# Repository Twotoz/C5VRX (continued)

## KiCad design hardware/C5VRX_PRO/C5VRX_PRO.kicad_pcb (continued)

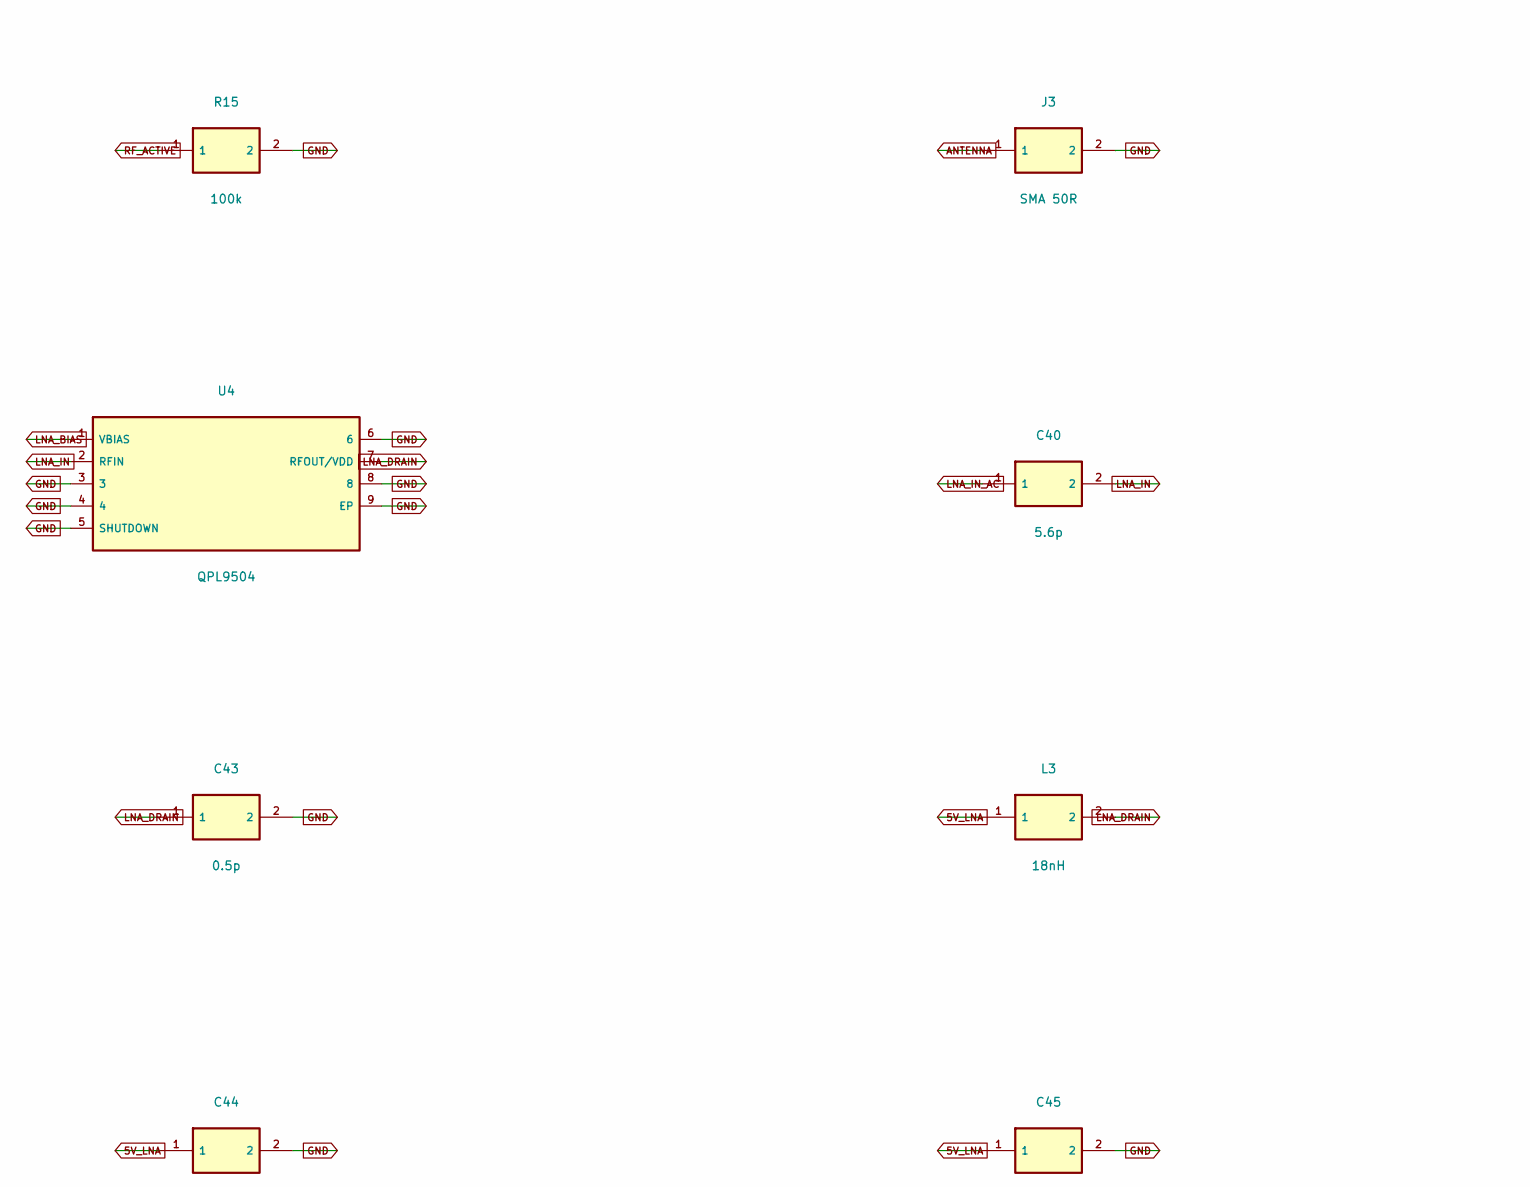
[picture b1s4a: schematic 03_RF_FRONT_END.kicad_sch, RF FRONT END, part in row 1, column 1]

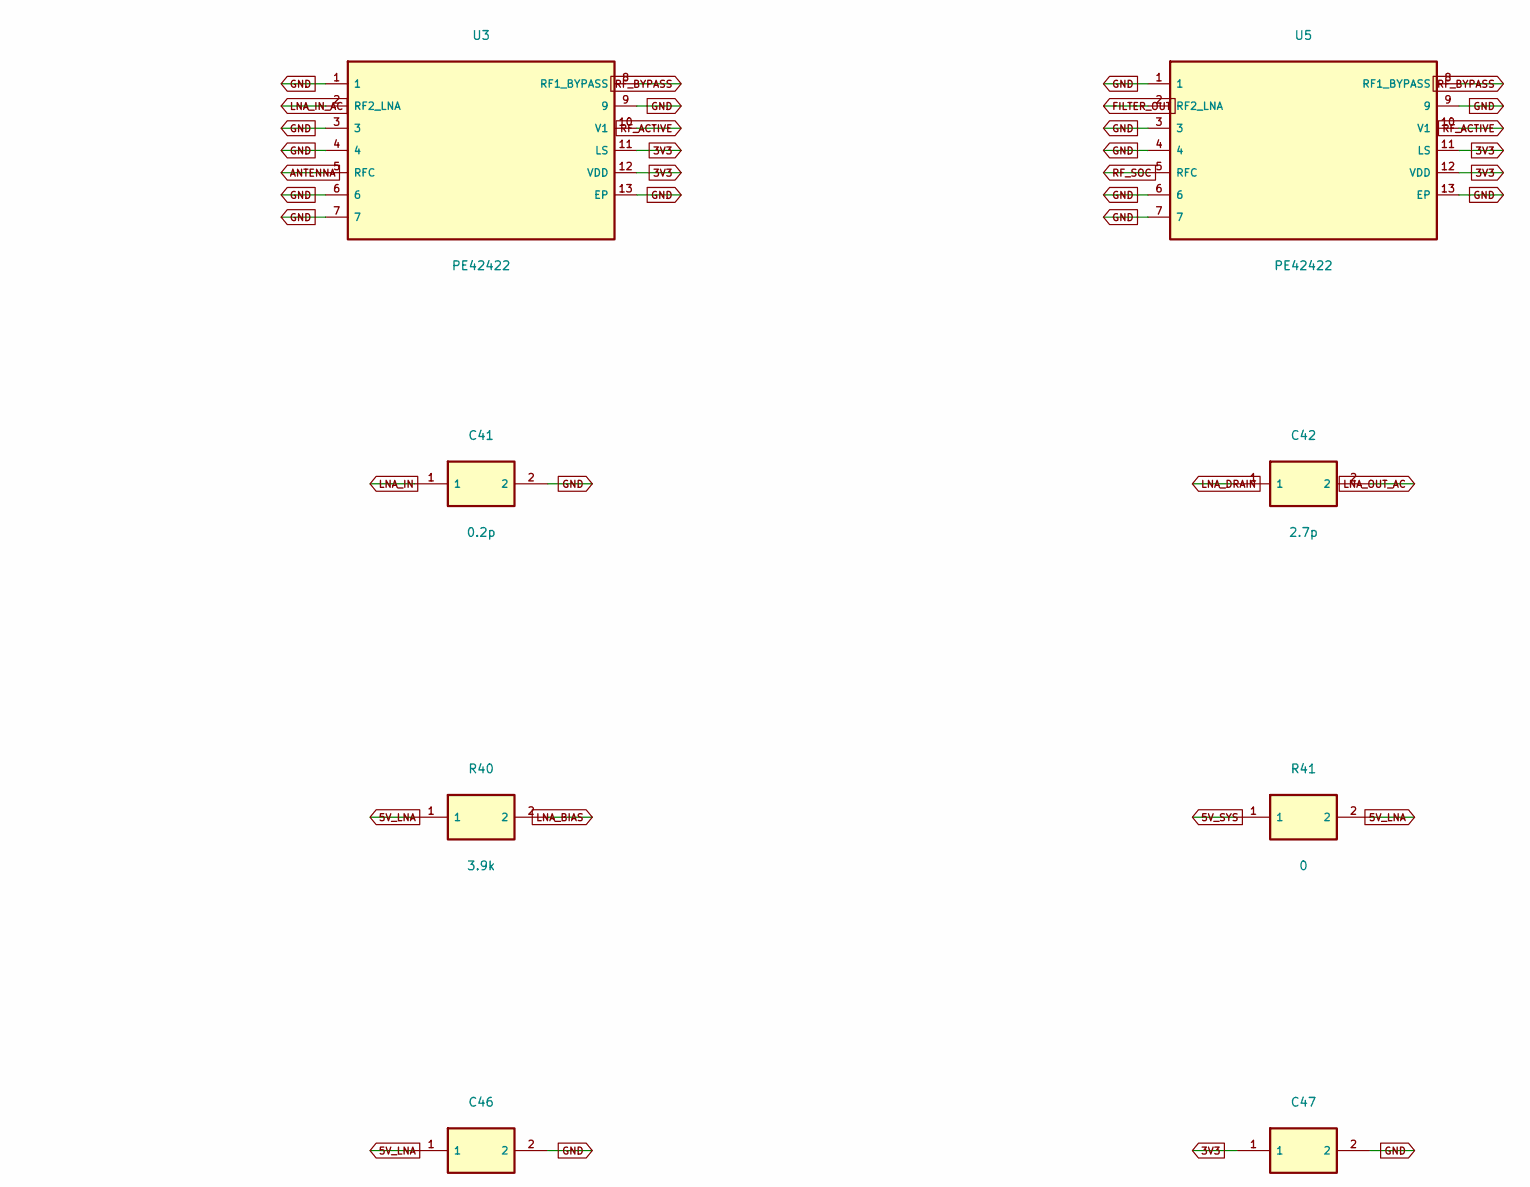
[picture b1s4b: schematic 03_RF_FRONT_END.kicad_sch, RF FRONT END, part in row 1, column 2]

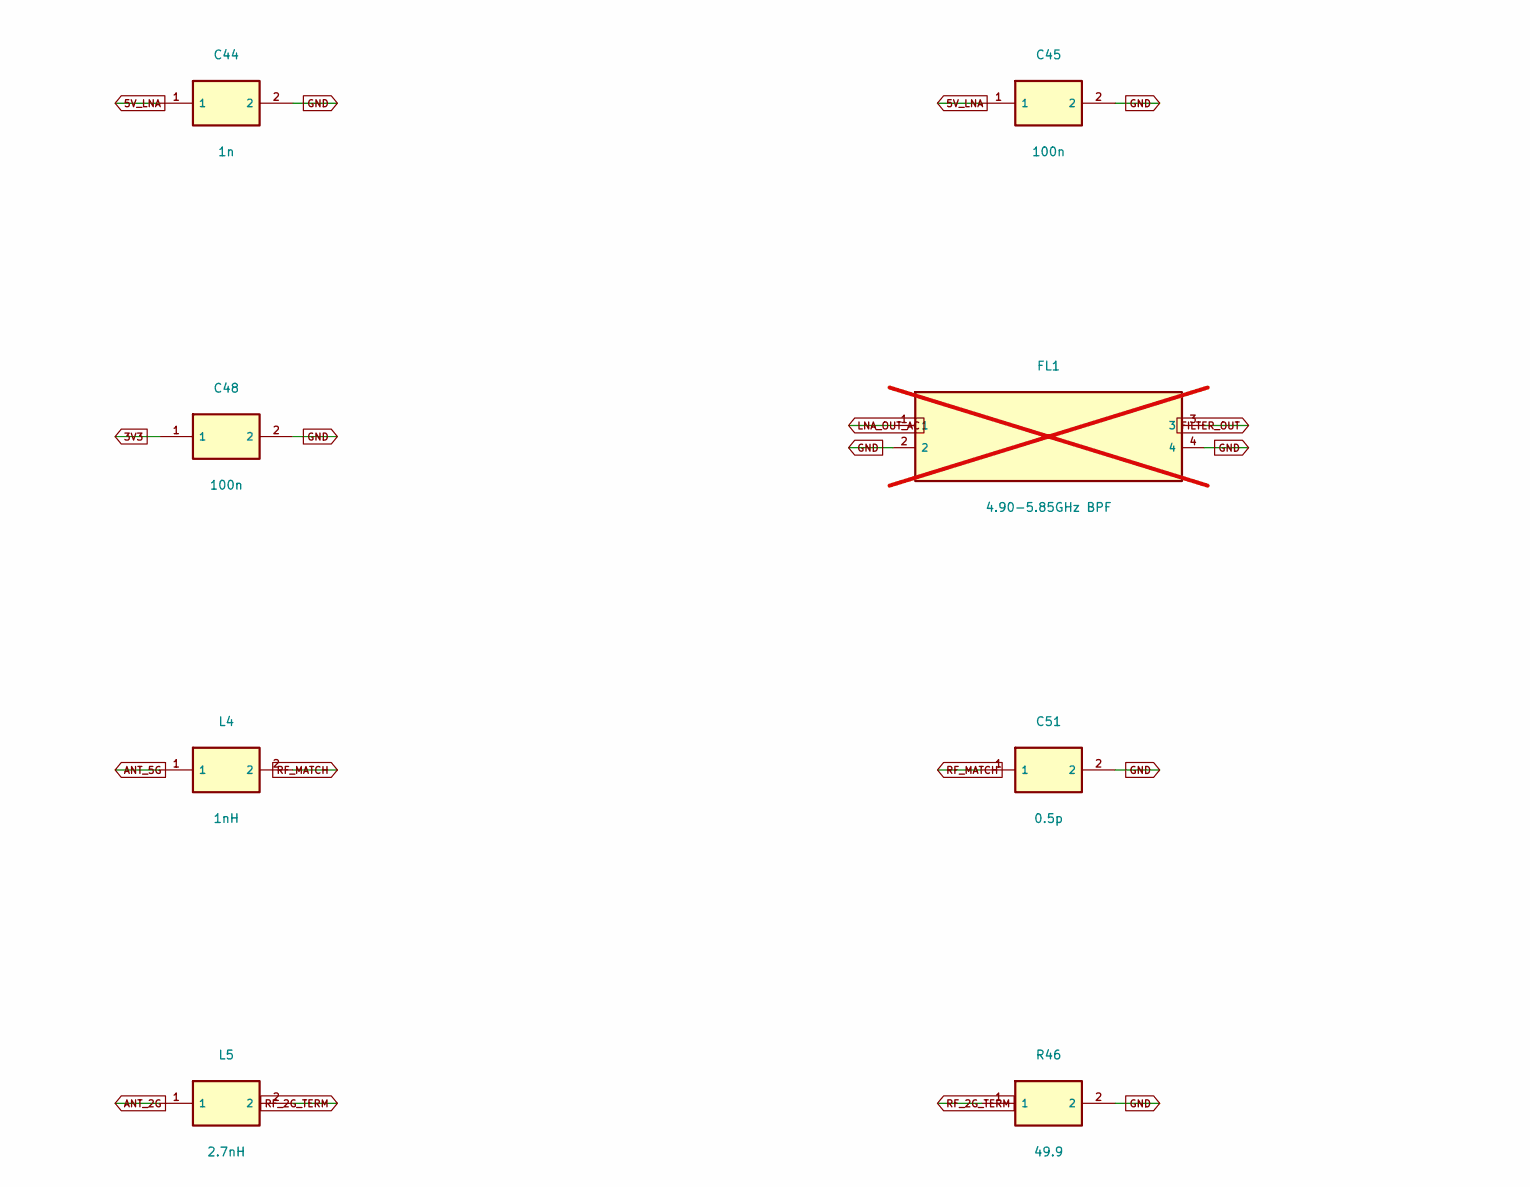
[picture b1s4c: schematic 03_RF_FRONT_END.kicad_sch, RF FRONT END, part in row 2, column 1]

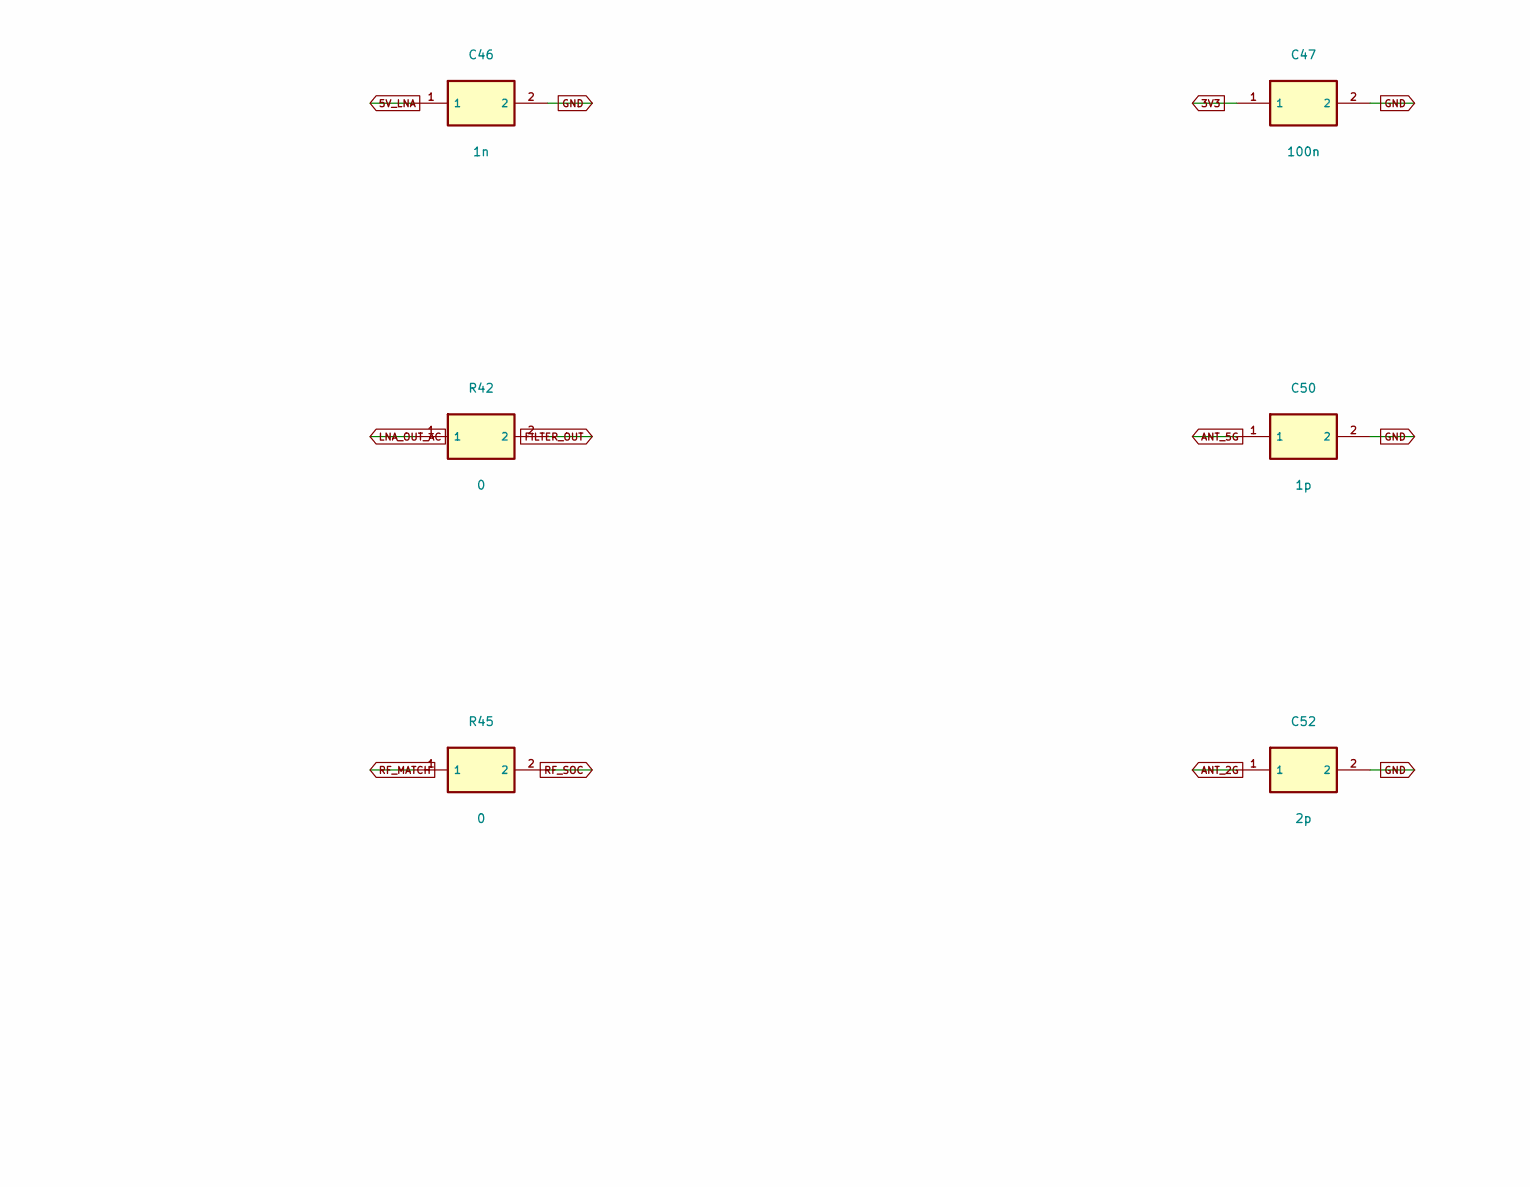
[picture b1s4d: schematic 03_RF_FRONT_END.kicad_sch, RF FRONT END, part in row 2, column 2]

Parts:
C40: 5.6p; Capacitor_SMD__C_0402_1005Metric; MPN GJM1555C1H5R6CB01D
C41: 0.2p; Capacitor_SMD__C_0402_1005Metric; MPN GJM1555C1HR20BB01D
C42: 2.7p; Capacitor_SMD__C_0402_1005Metric; MPN GJM1555C1H2R7CB01D
C43: 0.5p; Capacitor_SMD__C_0402_1005Metric; MPN GJM1555C1HR50BB01D
C44, C46: 1n; Capacitor_SMD__C_0402_1005Metric; MPN GRM155R71H102KA01D
C45, C47, C48: 100n; Capacitor_SMD__C_0402_1005Metric; MPN GRM155R71C104KA88D
C50: 1p; Capacitor_SMD__C_0201_0603Metric; MPN GRM0335C1H1R0CA01D
C51: 0.5p; Capacitor_SMD__C_0201_0603Metric; MPN GRM0335C1HR50BA01D
C52: 2p; Capacitor_SMD__C_0201_0603Metric; MPN GRM0335C1H2R0CA01D
FL1: 4.90-5.85GHz BPF; LFB215G37; MPN LFB215G37SG8A180; not fitted
J3: SMA 50R; Connector_Coaxial__SMA_Amphenol_132134_Vertical; MPN 132134
L3: 18nH; Inductor_SMD__L_0603_1608Metric; MPN 0603CS-18NXJRU
L4: 1nH; Inductor_SMD__L_0201_0603Metric; MPN LQP03TN1N0B02D
L5: 2.7nH; Inductor_SMD__L_0201_0603Metric; MPN LQP03TN2N7B02D
R15: 100k; Resistor_SMD__R_0402_1005Metric; MPN RC0402FR-07100KL
R40: 3.9k; Resistor_SMD__R_0402_1005Metric; MPN RC0402FR-073K9L
R41, R42, R45: 0; Resistor_SMD__R_0402_1005Metric; MPN RC0402JR-070RL
R46: 49.9; Resistor_SMD__R_0603_1608Metric; MPN RC0603FR-0749R9L
U3, U5: PE42422; PE42422_QFN12; MPN PE42422A-X
U4: QPL9504; QPL9504_DFN8; MPN QPL9504TR7

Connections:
3V3: C47.1, C48.1, U3.11 (LS), U3.12 (VDD), U5.11 (LS), U5.12 (VDD); also elsewhere on the board
5V_LNA: C44.1, C45.1, C46.1, L3.1, R40.1, R41.2
5V_SYS: R41.1; also elsewhere on the board
ANTENNA: J3.1, U3.5 (RFC)
ANT_2G: C52.1, L5.1; also elsewhere on the board
ANT_5G: C50.1, L4.1; also elsewhere on the board
FILTER_OUT: FL1.3, R42.2, U5.2 (RF2_LNA)
GND: C41.2, C43.2, C44.2, C45.2, C46.2, C47.2, C48.2, C50.2, C51.2, C52.2, FL1.2, FL1.4, J3.2, R15.2, R46.2, U3.1, U3.3, U3.4, U3.6, U3.7, U3.9, U3.13 (EP), U4.3, U4.4, U4.5 (SHUTDOWN), U4.6, U4.8, U4.9 (EP), U5.1, U5.3, U5.4, U5.6, U5.7, U5.9, U5.13 (EP); also elsewhere on the board
LNA_BIAS: R40.2, U4.1 (VBIAS)
LNA_DRAIN: C42.1, C43.1, L3.2, U4.7 (RFOUT/VDD)
LNA_IN: C40.2, C41.1, U4.2 (RFIN)
LNA_IN_AC: C40.1, U3.2 (RF2_LNA)
LNA_OUT_AC: C42.2, FL1.1, R42.1
RF_2G_TERM: L5.2, R46.1
RF_ACTIVE: R15.1, U3.10 (V1), U5.10 (V1); also elsewhere on the board
RF_BYPASS: U3.8 (RF1_BYPASS), U5.8 (RF1_BYPASS)
RF_MATCH: C51.1, L4.2, R45.1
RF_SOC: R45.2, U5.5 (RFC)

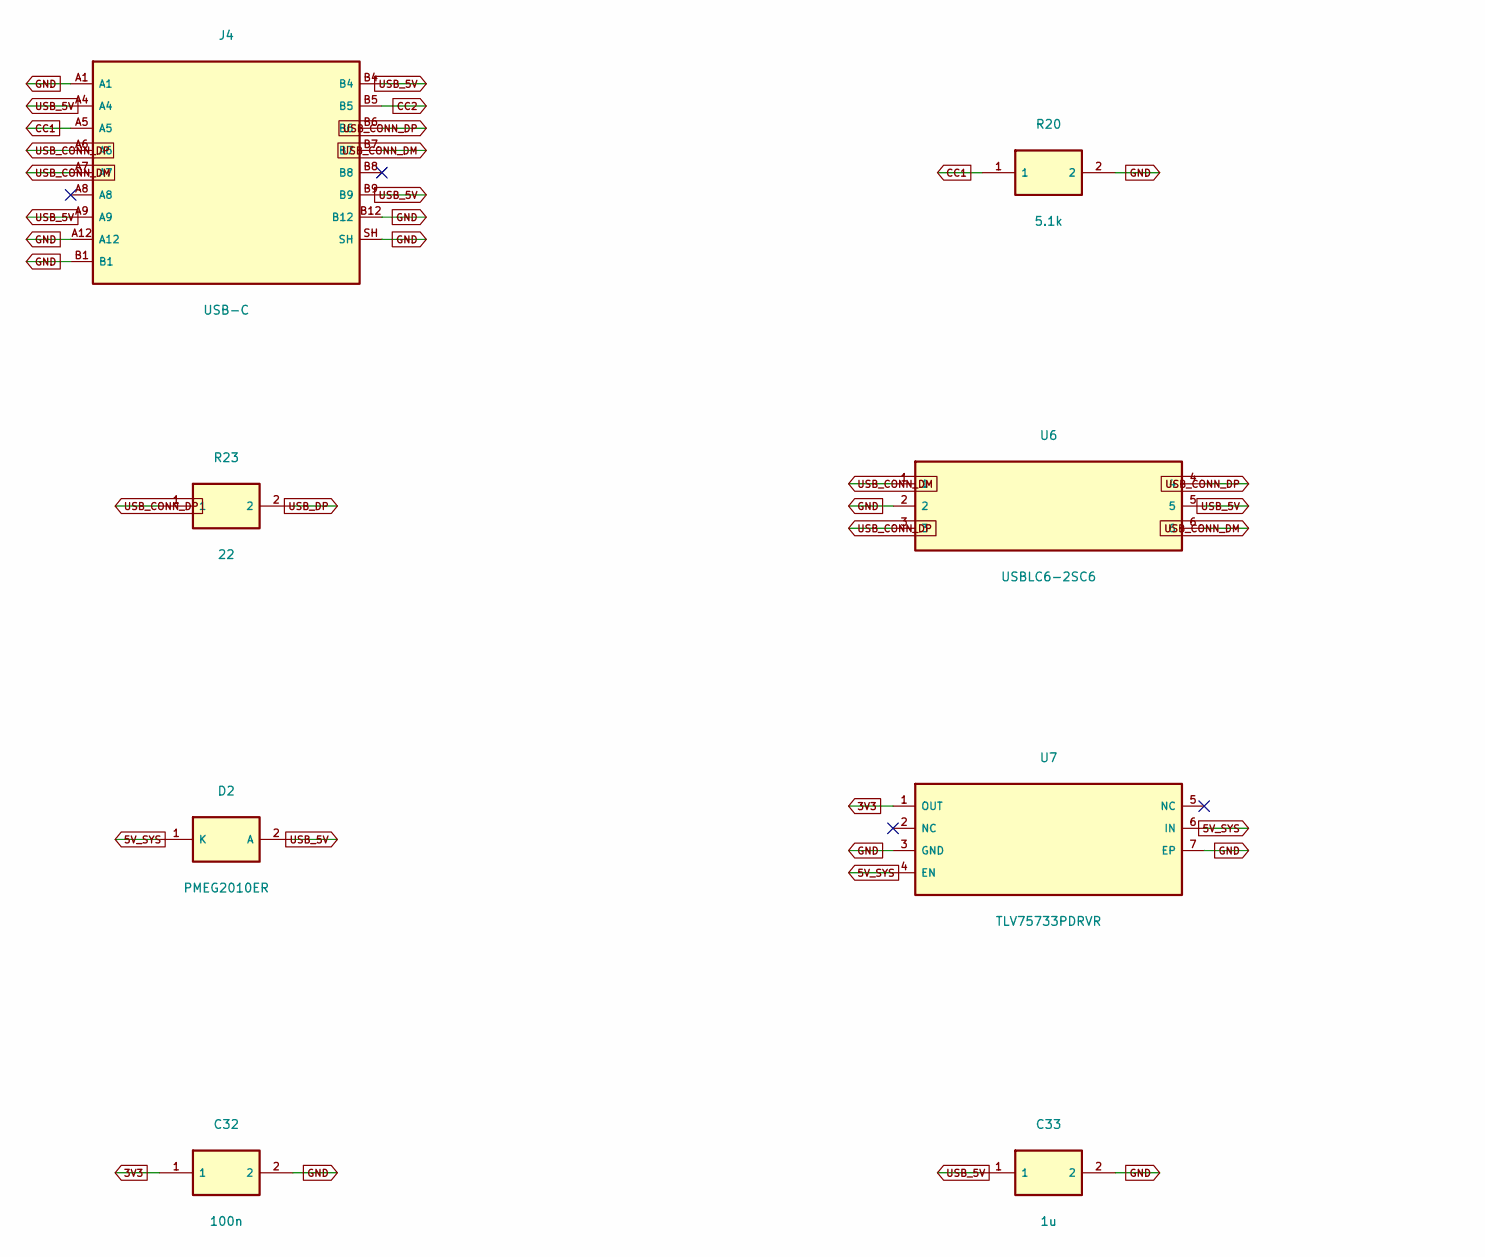
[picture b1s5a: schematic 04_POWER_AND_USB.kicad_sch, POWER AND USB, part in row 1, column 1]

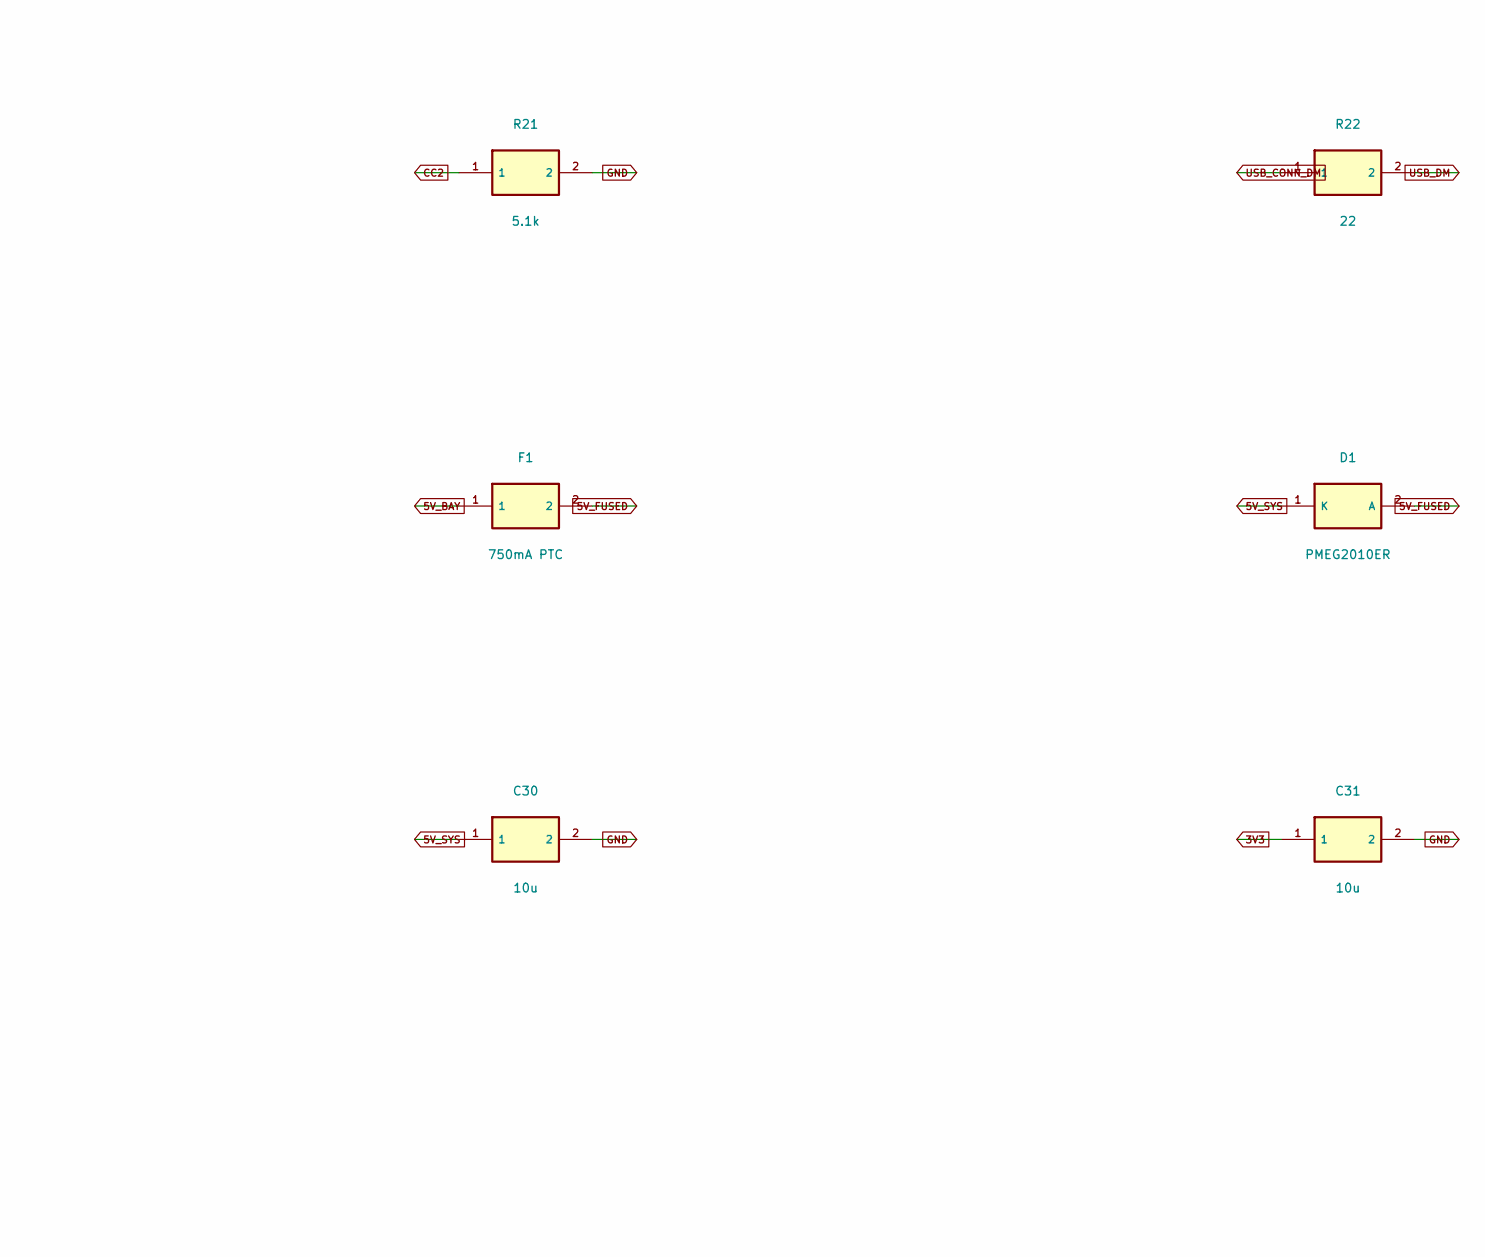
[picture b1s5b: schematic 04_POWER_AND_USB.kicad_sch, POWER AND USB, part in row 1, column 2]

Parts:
C30, C31: 10u; Capacitor_SMD__C_0603_1608Metric; MPN GRM188R61A106KE69D
C32: 100n; Capacitor_SMD__C_0402_1005Metric; MPN GRM155R71C104KA88D
C33: 1u; Capacitor_SMD__C_0402_1005Metric; MPN GRM155R61A105KE15D
D1, D2: PMEG2010ER; Diode_SMD__Nexperia_CFP3_SOD-123W; MPN PMEG2010ER,115
F1: 750mA PTC; Fuse__Fuse_1206_3216Metric; MPN 1206L075/13.2WR
J4: USB-C; Connector_USB__USB_C_Receptacle_HRO_TYPE-C-31-M-12; MPN TYPE-C-31-M-12
R20, R21: 5.1k; Resistor_SMD__R_0402_1005Metric; MPN RC0402FR-075K1L
R22, R23: 22; Resistor_SMD__R_0402_1005Metric; MPN RC0402FR-0722RL
U6: USBLC6-2SC6; Package_TO_SOT_SMD__SOT-23-6; MPN USBLC6-2SC6
U7: TLV75733PDRVR; Package_DFN_QFN__DFN-6-1EP_2x2mm_P0.65mm_EP1x1.6mm; MPN TLV75733PDRVR

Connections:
3V3: C31.1, C32.1, U7.1 (OUT); also elsewhere on the board
5V_BAY: F1.1; also elsewhere on the board
5V_FUSED: D1.2 (A), F1.2
5V_SYS: C30.1, D1.1 (K), D2.1 (K), U7.4 (EN), U7.6 (IN); also elsewhere on the board
CC1: J4.A5, R20.1
CC2: J4.B5, R21.1
GND: C30.2, C31.2, C32.2, C33.2, J4.A1, J4.A12, J4.B1, J4.B12, J4.SH, R20.2, R21.2, U6.2, U7.3 (GND), U7.7 (EP); also elsewhere on the board
USB_5V: C33.1, D2.2 (A), J4.A4, J4.A9, J4.B4, J4.B9, U6.5
USB_CONN_DM: J4.A7, J4.B7, R22.1, U6.1, U6.6
USB_CONN_DP: J4.A6, J4.B6, R23.1, U6.3, U6.4
USB_DM: R22.2; also elsewhere on the board
USB_DP: R23.2; also elsewhere on the board

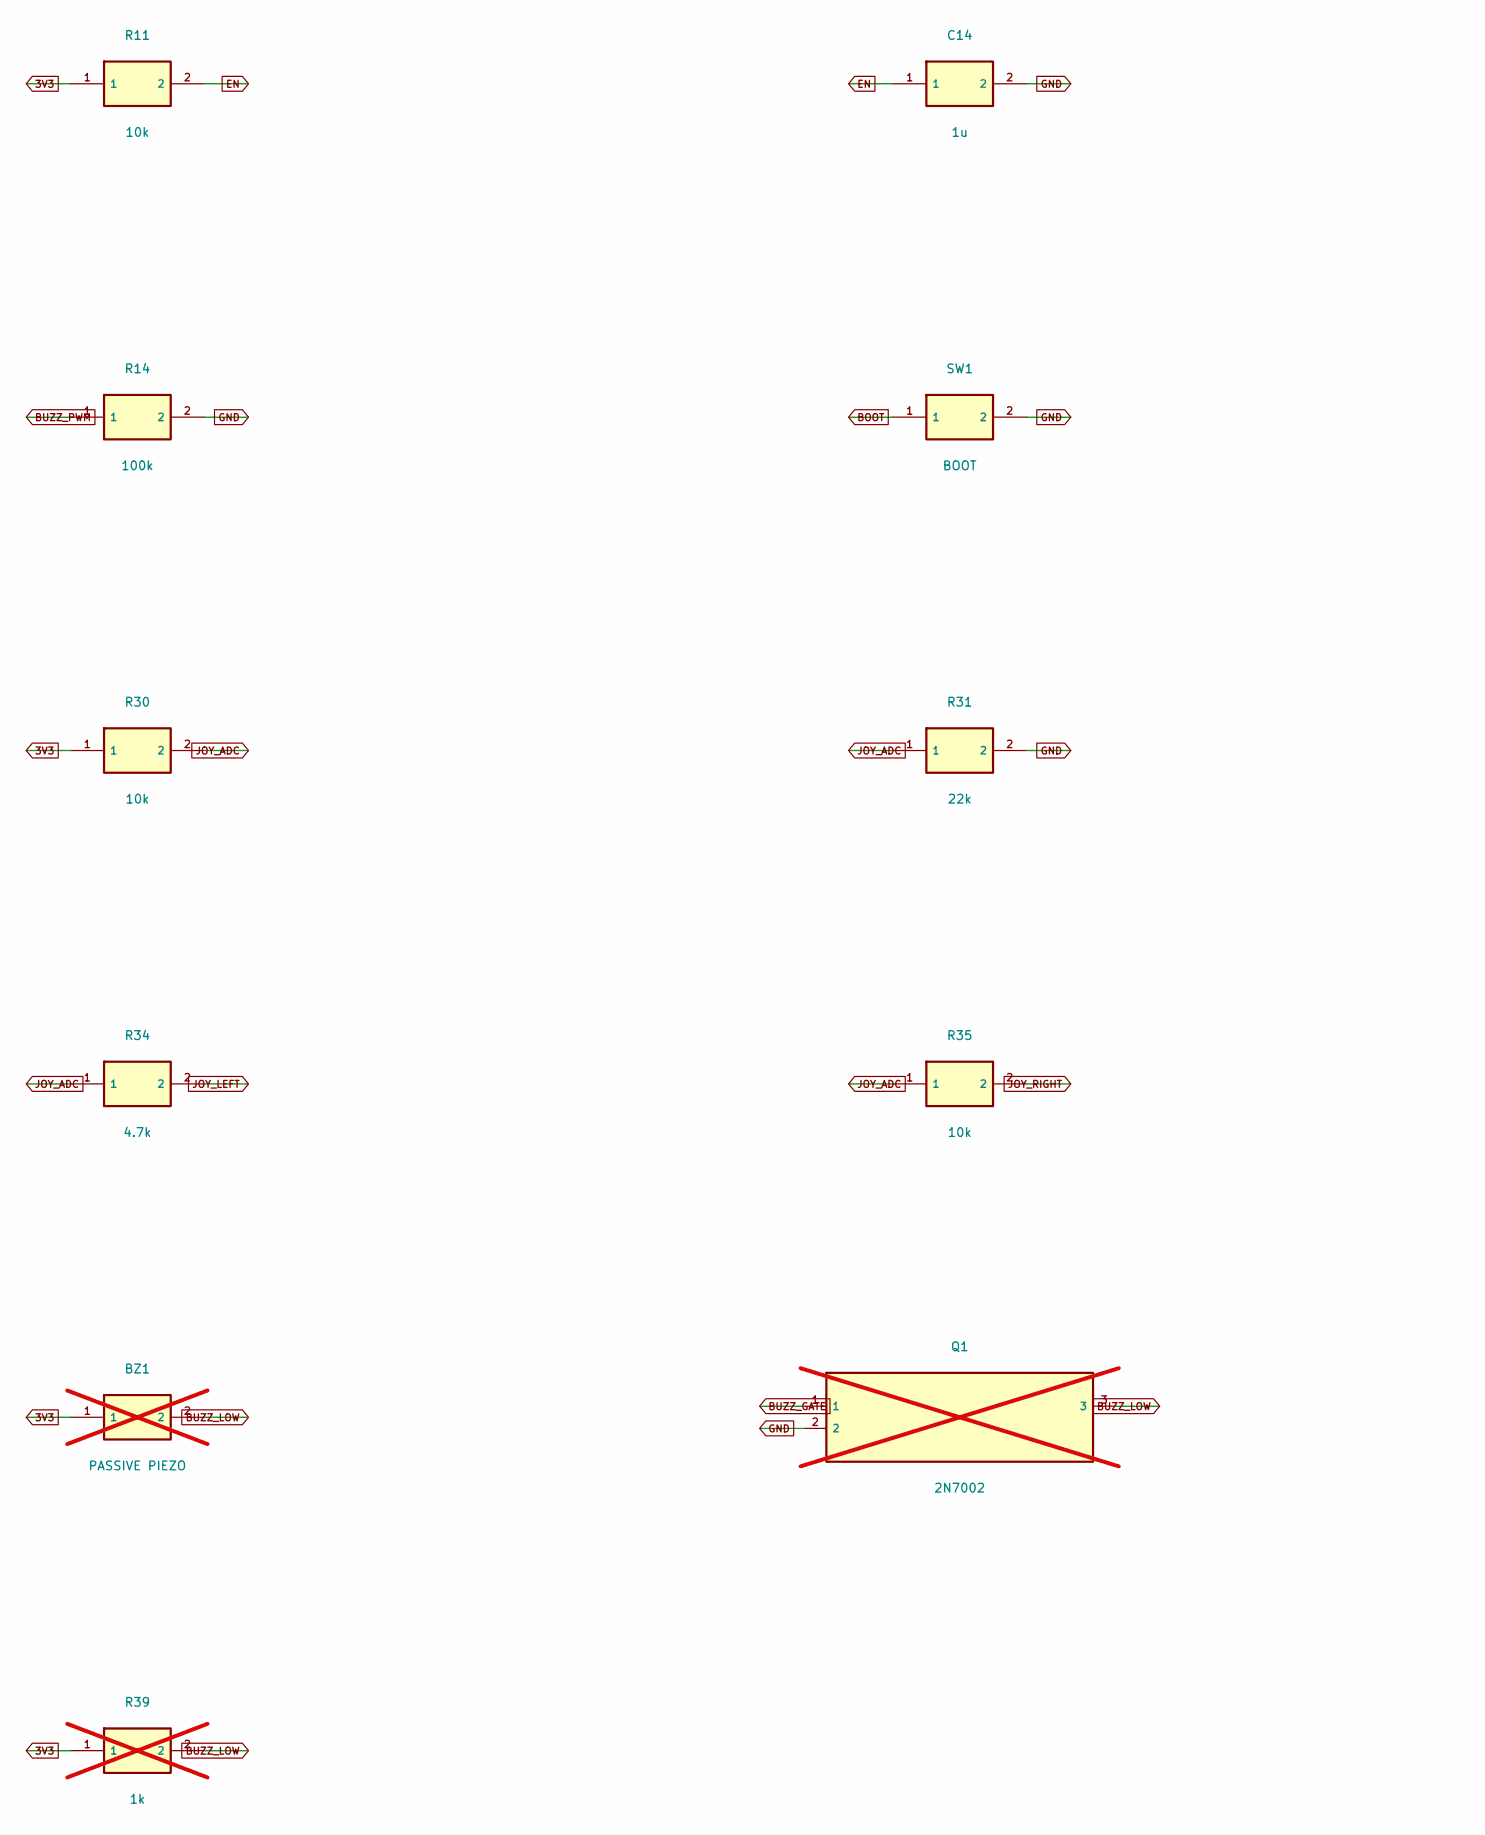
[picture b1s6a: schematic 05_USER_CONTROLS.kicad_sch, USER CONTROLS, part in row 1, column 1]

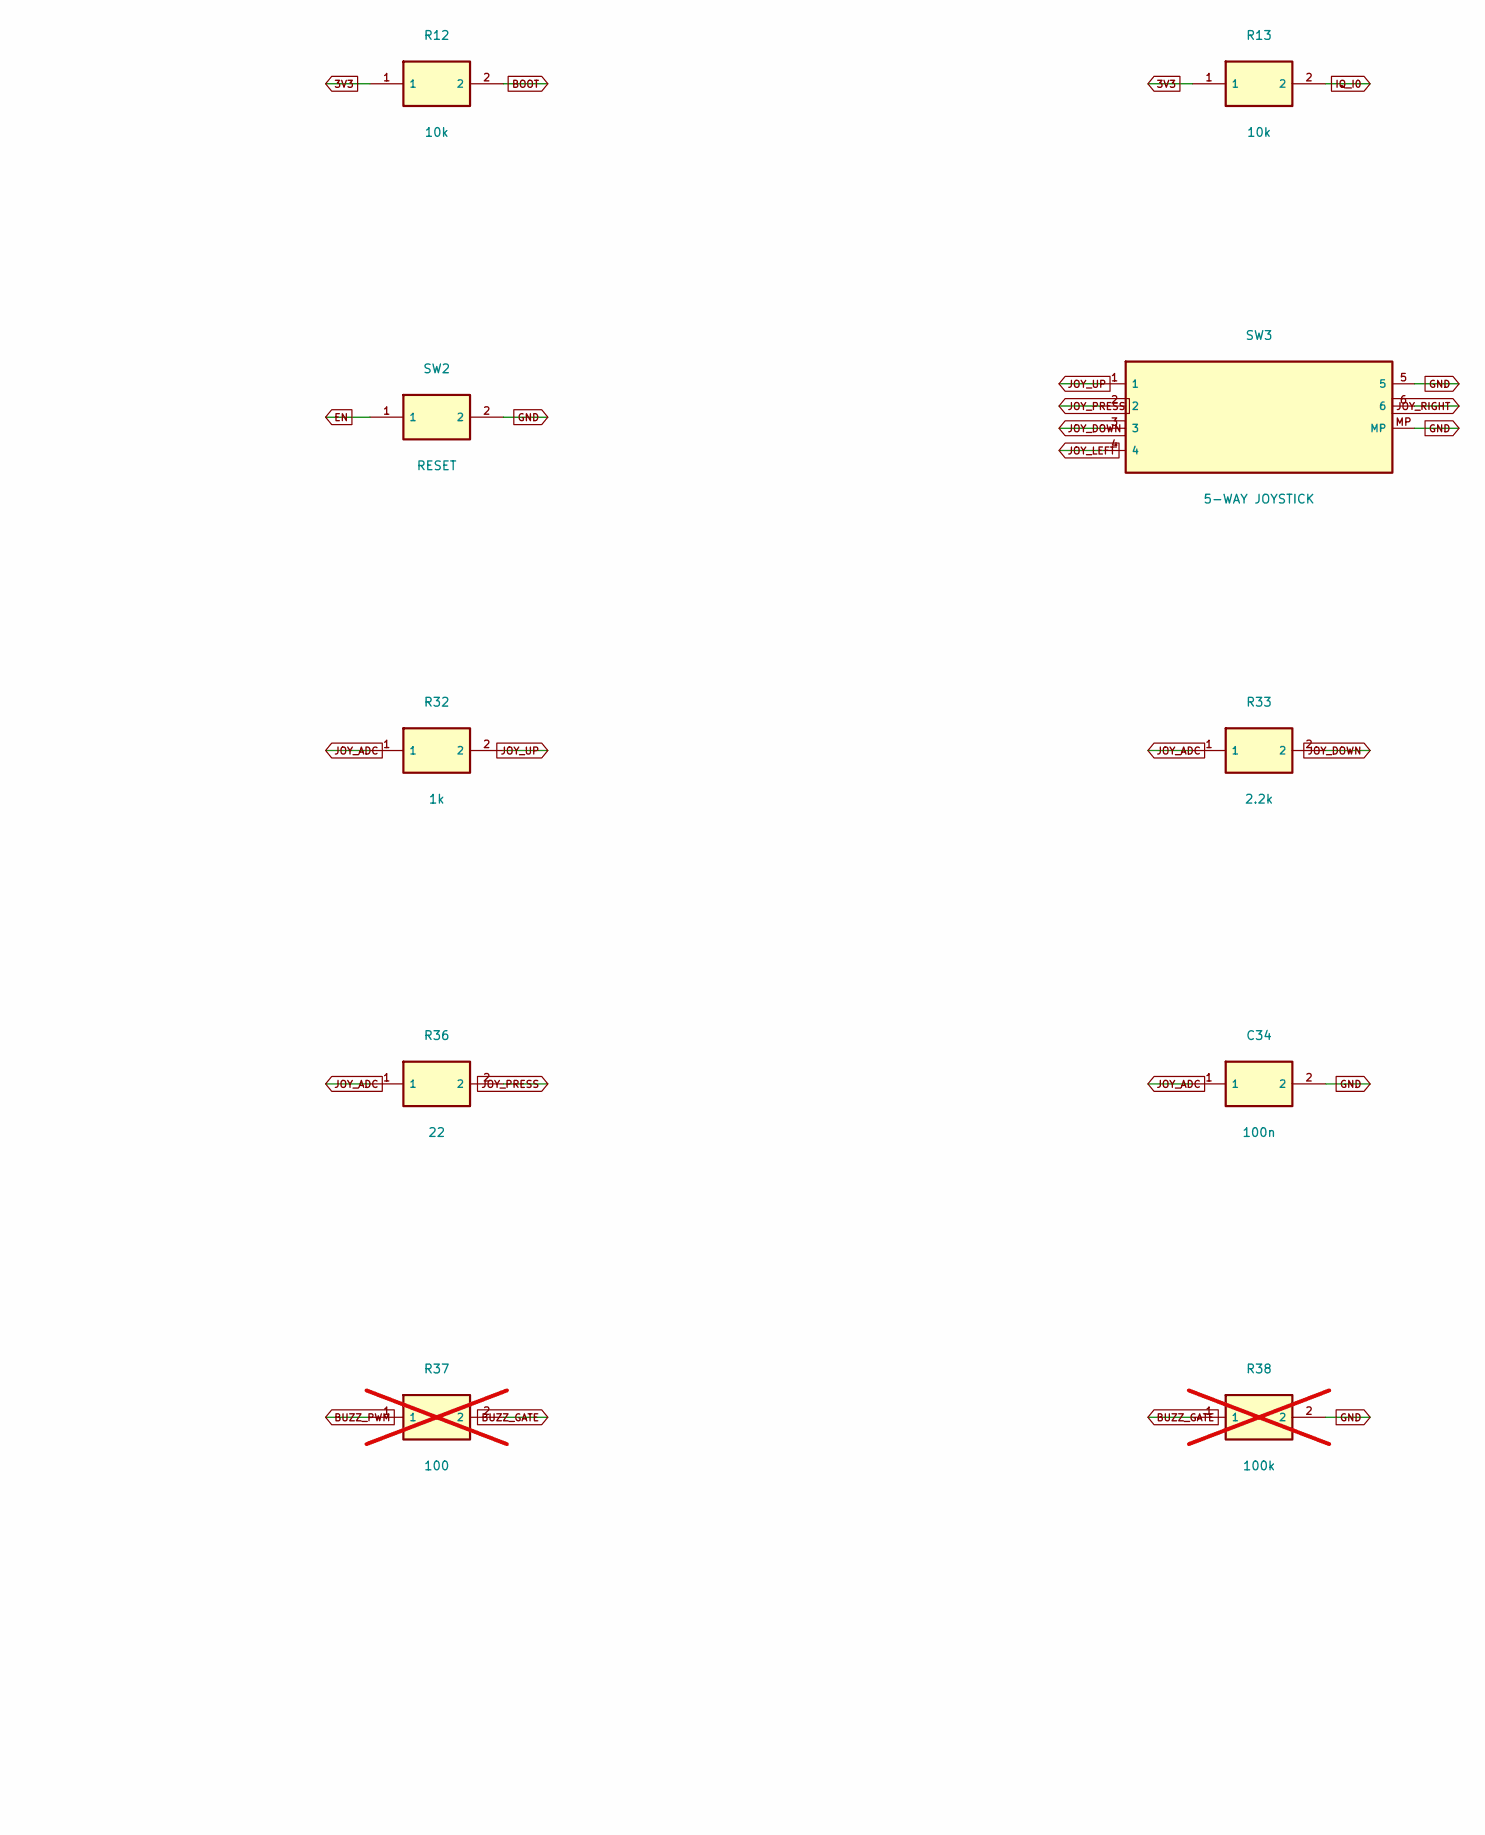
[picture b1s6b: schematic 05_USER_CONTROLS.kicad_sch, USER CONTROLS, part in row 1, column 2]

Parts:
BZ1: PASSIVE PIEZO; Buzzer_Beeper__Buzzer_Murata_PKLCS1212E; MPN PKLCS1212E4001-R1; not fitted
C14: 1u; Capacitor_SMD__C_0402_1005Metric; MPN GRM155R61A105KE15D
C34: 100n; Capacitor_SMD__C_0402_1005Metric; MPN GRM155R71C104KA88D
Q1: 2N7002; Package_TO_SOT_SMD__SOT-23; MPN 2N7002,215; not fitted
R11, R12, R13, R30, R35: 10k; Resistor_SMD__R_0402_1005Metric; MPN RC0402FR-0710KL
R14: 100k; Resistor_SMD__R_0402_1005Metric; MPN RC0402FR-07100KL
R31: 22k; Resistor_SMD__R_0402_1005Metric; MPN RC0402FR-0722KL
R32: 1k; Resistor_SMD__R_0402_1005Metric; MPN RC0402FR-071KL
R33: 2.2k; Resistor_SMD__R_0402_1005Metric; MPN RC0402FR-072K2L
R34: 4.7k; Resistor_SMD__R_0402_1005Metric; MPN RC0402FR-074K7L
R36: 22; Resistor_SMD__R_0402_1005Metric; MPN RC0402FR-0722RL
R37: 100; Resistor_SMD__R_0402_1005Metric; MPN RC0402FR-07100RL; not fitted
R38: 100k; Resistor_SMD__R_0402_1005Metric; MPN RC0402FR-07100KL; not fitted
R39: 1k; Resistor_SMD__R_0402_1005Metric; MPN RC0402FR-071KL; not fitted
SW1: BOOT; Button_Switch_SMD__SW_SPST_B3U-1000P; MPN B3U-1000P
SW2: RESET; Button_Switch_SMD__SW_SPST_B3U-1000P; MPN B3U-1000P
SW3: 5-WAY JOYSTICK; SW_SKRHABE010_SMD; MPN SKRHABE010

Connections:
3V3: BZ1.1, R11.1, R12.1, R13.1, R30.1, R39.1; also elsewhere on the board
BOOT: R12.2, SW1.1; also elsewhere on the board
BUZZ_GATE: Q1.1, R37.2, R38.1
BUZZ_LOW: BZ1.2, Q1.3, R39.2
BUZZ_PWM: R14.1, R37.1; also elsewhere on the board
EN: C14.1, R11.2, SW2.1; also elsewhere on the board
GND: C14.2, C34.2, Q1.2, R14.2, R31.2, R38.2, SW1.2, SW2.2, SW3.5, SW3.MP; also elsewhere on the board
IQ_I0: R13.2; also elsewhere on the board
JOY_ADC: C34.1, R30.2, R31.1, R32.1, R33.1, R34.1, R35.1, R36.1; also elsewhere on the board
JOY_DOWN: R33.2, SW3.3
JOY_LEFT: R34.2, SW3.4
JOY_PRESS: R36.2, SW3.2
JOY_RIGHT: R35.2, SW3.6
JOY_UP: R32.2, SW3.1
